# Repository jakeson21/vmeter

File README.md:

# vmeter
Digital voltmeter circuit design based on an ICL7107

# Description
This circuit is centered around the ICL7107, a single-chip digital voltmeter with features an integrated 3.1 7-segment LED display driver. MY purpose designing and building this was to use it in my homemade bench top power supply as a readout for the (-)12V-0V and 0V-12V variable supplies. The first iteration used all through hole components. This design uses mostly surface mount components.

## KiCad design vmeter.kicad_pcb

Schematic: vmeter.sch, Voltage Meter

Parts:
C1: 100pF
C2: 100nF
C3: 220nF
C4: 470nF
C5: 10nF
CP6, CP7: 10uF
D1, D2: 1N4148
DS1, DS2: LED_DUAL7SEG_ACDA04
J1: TP1
J2: MEAS
J3: PWR_IN
J4: HEADER_3
J5: TP3
J6: TP2
J7: TP5
J8: TP4
R1, R3: 100k
R2: 47k
R4: 15K
R5: 220
R6: 10k
RV1: 10K
U1: ICL7107CM44Z
U2: ICL7660CBAZ

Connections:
+5V: D2.1 (A), J3.2, J4.3, R4.2, U1.8 (V+), U2.8 (V+)
/-5V: CP7.1, J4.1, U1.34 (V-), U2.5 (VOUT)
/A2: DS2.17 (a1), U1.19 (A2)
/B2: DS2.16 (b1), U1.18 (B2)
/C2: DS2.4 (c1), U1.17 (C2)
/CA: D1.2 (K), DS1.3 (CA), DS1.8 (CA), DS1.13 (CA), DS1.18 (CA), DS2.3 (CA), DS2.8 (CA), DS2.13 (CA), DS2.18 (CA)
/D2: DS2.2 (d1), U1.16 (D2)
/E2: DS2.1 (e1), U1.21 (E2)
/F2: DS2.19 (f1), U1.20 (F2)
/G2: DS2.20 (g1), U1.32 (G2)
/V+meas: J2.1, R3.2
GND: C5.1, CP7.2, J2.2, J3.1, J4.2, R5.1, R6.1, U1.28 (BP/GND), U1.38 (IN_LO), U2.3 (GND)
unnamed: DS1.12 (a2), U1.30 (A3)
unnamed: DS1.16 (b1), DS1.17 (a1), U1.26 (AB4)
unnamed: DS1.15 (g2), U1.29 (G3)
unnamed: DS1.14 (f2), U1.24 (F3)
unnamed: DS1.11 (b2), U1.23 (B3)
unnamed: DS1.20 (g1), U1.27 (POL)
unnamed: DS1.7 (d2), U1.22 (D3)
unnamed: DS1.6 (e2), U1.25 (E3)
unnamed: DS2.15 (g2), U1.14 (G1)
unnamed: DS2.14 (f2), U1.13 (F1)
unnamed: DS2.12 (a2), U1.12 (A1)
unnamed: DS2.11 (b2), U1.11 (B1)
unnamed: DS2.9 (c2), U1.10 (C1)
unnamed: DS2.7 (d2), U1.9 (D1)
unnamed: DS2.6 (e2), U1.15 (E1)
unnamed: DS1.10 (DP2), R5.2
unnamed: J5.1, RV1.1, U1.40 (COMM), U1.43 (REF_LO)
unnamed: D1.1 (A), D2.2 (K)
unnamed: DS1.9 (c2), U1.31 (C3)
unnamed: C5.2, R3.1, R6.2, U1.39 (IN_HI)
unnamed: C1.2, J7.1, R1.2, U1.7 (OSC_1)
unnamed: R1.1, U1.6 (OSC_2)
unnamed: C1.1, U1.4 (OCS_3)
unnamed: J1.1, U1.3 (TEST)
unnamed: CP6.2, U2.4 (CAP-)
unnamed: R2.1, U1.36 (BUFF)
unnamed: C3.2, J8.1, U1.35 (INT)
unnamed: J6.1, RV1.2, U1.44 (REF_HI)
unnamed: R4.1, RV1.3
unnamed: CP6.1, U2.2 (CAP+)
unnamed: C2.1, U1.42 (CREF+)
unnamed: C4.2, U1.37 (A-Z)
unnamed: C3.1, C4.1, R2.2
unnamed: C2.2, U1.41 (CREF-)

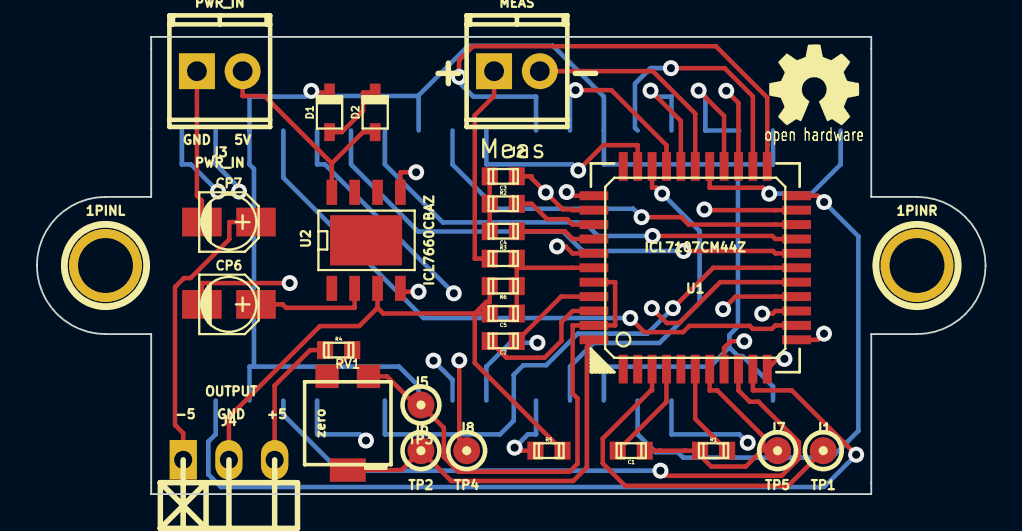
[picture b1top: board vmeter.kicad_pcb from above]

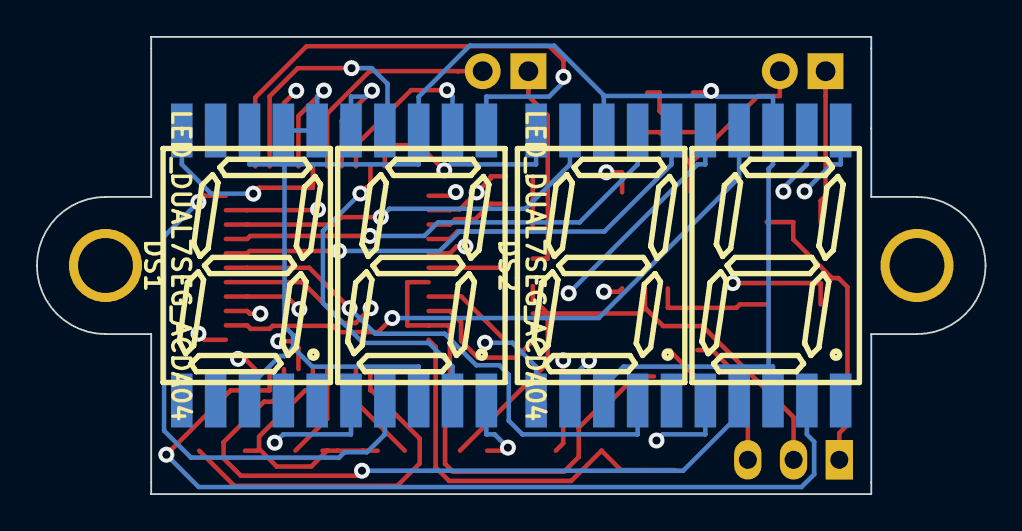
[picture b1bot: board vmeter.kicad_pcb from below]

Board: 4 copper layers, 52.7 x 25.4 mm, 30 parts (2 on the bottom side), 46 nets.

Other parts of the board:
1PINL, 1PINR: P***; 1pin

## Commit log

2015-06-16 Initial add and commit of project
2015-06-16 Updated README
    added to README.md
